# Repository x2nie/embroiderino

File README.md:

# Embroiderino 
Embroiderino is a test project which aims at providing all needed to turn an ordinary sewing machine into digital embroidery machine or at least to reuse any other embroidery machine with mainboard failure. Most of the mechanical parts are intended to be made on 3D printer.

As an electronics, arduio based 3D printer board is tested, with additional encoders connected to it. [This](https://gitlab.com/markol/XYprotoboard) will do job for now too. As a firmware
[teathimble](https://gitlab.com/markol/Teathimble_Firmware) is in development. For hoop positioning [this plotter](https://gitlab.com/markol/Simple_plotter) is adopted. All mechanics parts and sewing machine itself are mounted to chipboard. 

Client application is written in python3 and TK, it can open CSV's created by [Embroidermodder2](https://github.com/Embroidermodder/Embroidermodder).

## Work in progress
Note that this is early stage development. Machine, main DC motor speed controller is a next milestone. All the code is licensed under GPL v3.

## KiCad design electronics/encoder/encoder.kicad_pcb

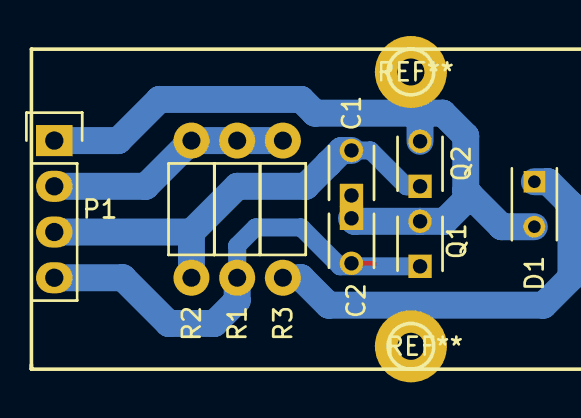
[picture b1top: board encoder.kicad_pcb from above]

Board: 2 copper layers, 9 parts (0 on the bottom side), 5 nets.

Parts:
C1, C2: 100n; C_Disc_D3_P2.5
D1: LED; C_Rect_L4_W2.5_P2.5
P1: CONN_01X04; Pin_Header_Straight_1x04
Q1, Q2: OPTO_NPN; C_Disc_D3_P2.5
R1, R2: 10K; Resistor_Horizontal_RM7mm
R3: 550R; Resistor_Horizontal_RM7mm

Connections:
GND: P1.2, R1.2, R2.2, R3.2
unnamed: C1.2, P1.3, Q2.1, R2.1
unnamed: C2.2, P1.4, Q1.1, R1.1
unnamed: D1.1, R3.1
VCC: C1.1, C2.1, D1.2, P1.1, Q1.2, Q2.2

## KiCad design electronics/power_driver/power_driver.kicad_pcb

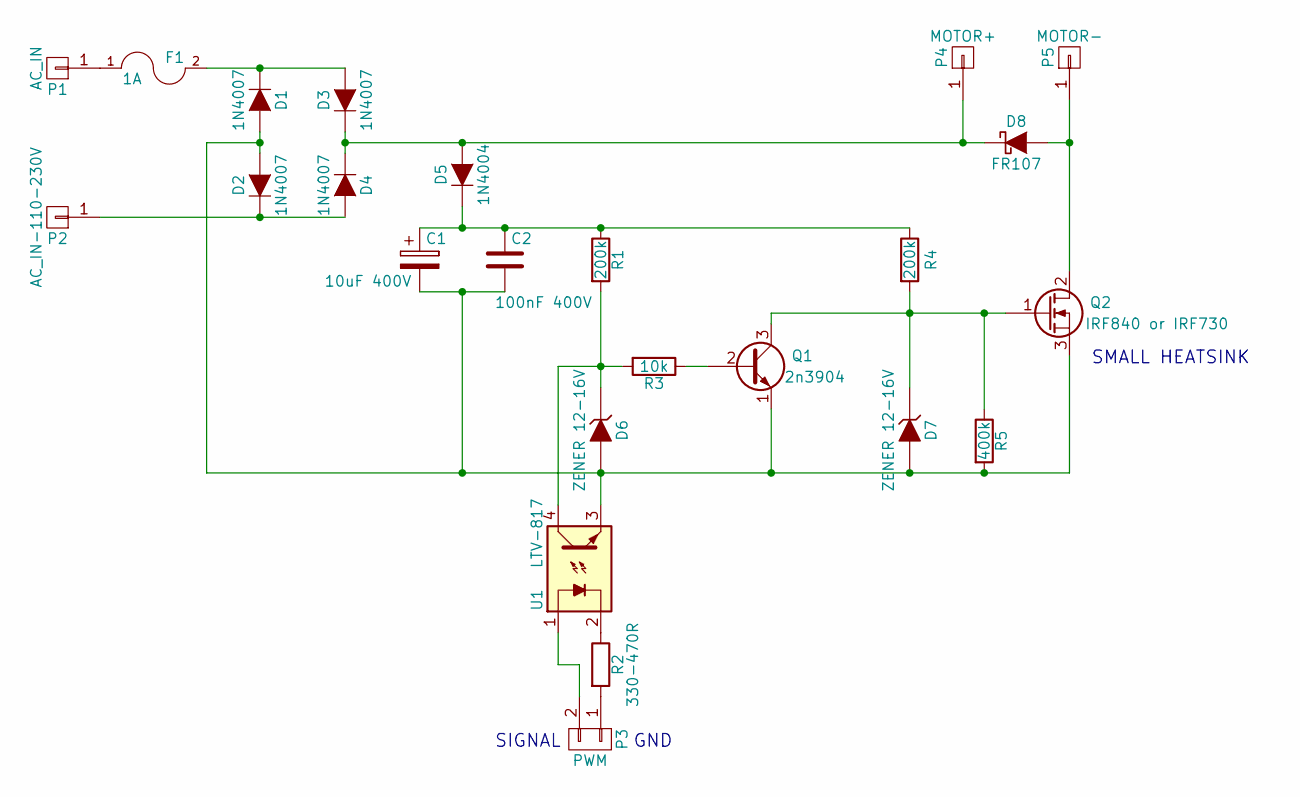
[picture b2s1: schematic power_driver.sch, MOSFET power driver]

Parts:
C1: 10uF 400V; C_Rect_L7_W4.5_P5
C2: 100nF 400V; C_Radial_D8_L11.5_P3.5
D1, D2, D3, D4: 1N4007; Diode_DO-41_SOD81_Horizontal_RM10
D5: 1N4004; Diode_DO-41_SOD81_Horizontal_RM10
D6, D7: ZENER 12-16V; Diode_DO-35_SOD27_Horizontal_RM10
D8: FR107; Diode_DO-41_SOD81_Horizontal_RM10
F1: 1A; Fuseholder5x20_horiz_open_inline_Type-I
P1: AC_IN; 1pin
P2: AC_IN-110-230V; 1pin
P3: PWM; Pin_Header_Straight_1x02
P4: MOTOR+; 1pin
P5: MOTOR-; 1pin
Q1: 2n3904; TO-92_Inline_Wide
Q2: IRF840 or IRF730; TO-220_Neutral123_Vertical
R1, R4: 200k; Resistor_Horizontal_RM7mm
R2: 330-470R; Resistor_Horizontal_RM7mm
R3: 10k; Resistor_Horizontal_RM7mm
R5: 400k; Resistor_Horizontal_RM7mm
U1: LTV-817; DIP-4_W7.62mm_LongPads

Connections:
unnamed: C1.1, C2.1, D5.1 (K), R1.1, R4.1
unnamed: C1.2, C2.2, D1.2 (A), D2.2 (A), D6.2 (A), D7.2 (A), Q1.1 (E), Q2.3 (S), R5.2, U1.3
unnamed: D1.1 (K), D3.2 (A), F1.2
unnamed: D2.1 (K), D4.2 (A), P2.1
unnamed: D3.1 (K), D4.1 (K), D5.2 (A), D8.1 (K), P4.1
unnamed: D6.1 (K), R1.2, R3.2, U1.4
unnamed: D7.1 (K), Q1.3 (C), Q2.1 (G), R4.2, R5.1
unnamed: D8.2 (A), P5.1, Q2.2 (D)
unnamed: F1.1, P1.1
unnamed: P3.1, R2.2
unnamed: P3.2, U1.1
unnamed: Q1.2 (B), R3.1
unnamed: R2.1, U1.2

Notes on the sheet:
SMALL HEATSINK
GND
SIGNAL

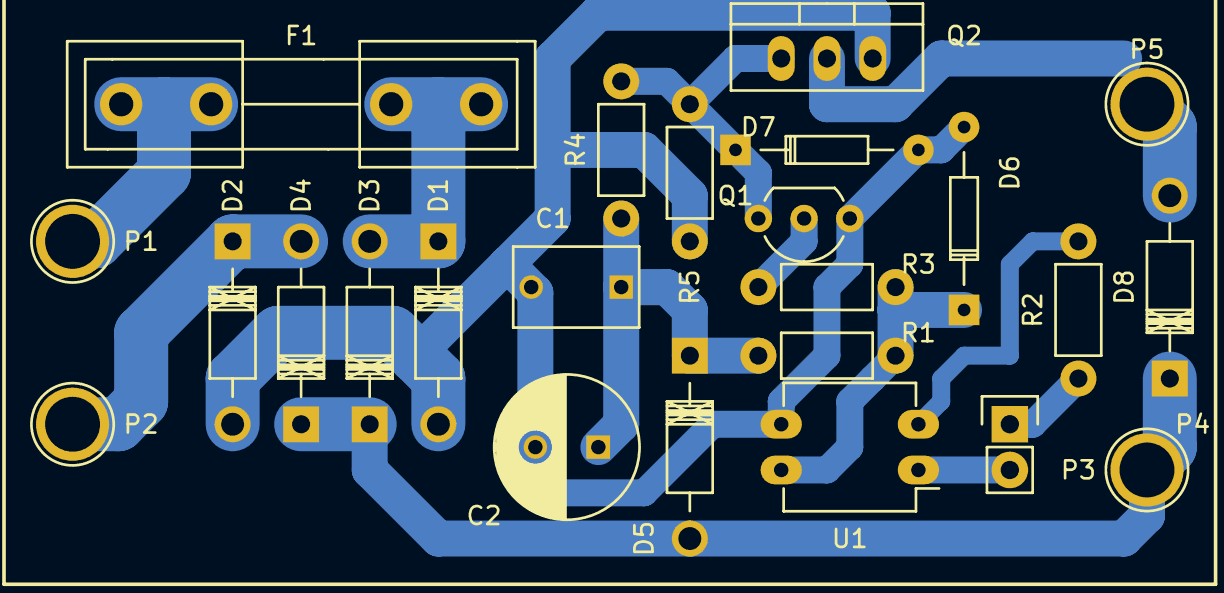
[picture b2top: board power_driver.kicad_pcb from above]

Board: 2 copper layers, 24 parts (0 on the bottom side), 13 nets.

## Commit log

2018-10-01 Inital commit, added client application and scad files.
2018-10-21 Added power driver PCB KiCad project.
2018-10-22 Added job auto pausing options, fixed job time estimation.
2018-10-25 Added speed control slider, design area check, exit confirm dialog fix, in progress percentage.
2018-10-30 Workarea origin parameter in hoop settings setup.
2018-11-04 Included sensor board KiCad files.
2018-11-09 Refactor of hoop scad code, minor changes in other models.
2018-11-10 Test design for large hoop.
2018-11-25 Machine hoops settings options for many selectable configurations.
2018-11-28 Added color change indicators and simulator mode from argv.
2018-11-30 Add LICENSE
2024-08-01 support CSV by pyembroidery
2024-08-01 support Embird csv
2024-08-01 gradient line drawing
2024-08-01 sample js to real serial-port (my = virtual port)
